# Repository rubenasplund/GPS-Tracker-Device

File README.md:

# GPS Tracker Device

## Project

The purpose for this project is to make a GPS tracker device which tracks position and movement patterns on animlas or things. Then sends the position data through lora.

## Areas of expertise

- Ruben will do the software
- Simon Will do the hardware

## Dependencies
- Install rust [https://rustup.rs/](https://rustup.rs/)

- Rust 1.40, or later

- `rustup update`

- `rustup target add thumbv7em-none-eabihf`

## Debug and Run

- `openocd -f openocd.cfg`

- `cargo run`

## Components

* GPS module - Adafruit 746 - https://www.elfa.se/en/mtk3339-gps-breakout-adafruit-746/p/30091220?q=GPS&pos=2&origPos=5&origPageSize=10&track=true

* Micro USB connector - https://www.elfa.se/en/micro-usb-with-solder-tabs-micro-usb-socket-right-angle-poles-molex-105017-0001/p/30161483?queryFromSuggest=true

* A display - SSD1306 SPI - https://cdon.se/hem-tradgard/oled-display-0-96-tum-vit-128x64-pixlar-ssd1306-spi-p50506639

* Temperature sensor - TMP36FSZ - https://se.rs-online.com/web/p/temperature-sensors-humidity-sensors/0412973/

* LED SMD 0805 - https://www.elfa.se/en/smd-led-640nm-0805-150mcd-20ma-kingbright-kp-2012surc/p/17531013?queryFromSuggest=true

* ADC - Integrated in MCU

* Battery (chargable) -ICP501022UPM - https://www.elfa.se/sv/litiumjonpolymerbatteripack-340mah-7v-renata-icp422339pr/p/30158712?q=&pos=1&origPos=1&origPageSize=10&track=true

* Charging circuit (for battery)- MCP73831T-2ACI/OT https://www.elfa.se/sv/laddkrets-75-sot-23-microchip-mcp73831t-2aci-ot/p/17386933?track=true&no-cache=true

* Button - https://www.elfa.se/en/tactile-switch-b3fs-1no-47n-6mm-omron-electronic-components-b3fs-1012p/p/30156578?q=smd+button&pos=3&origPos=43&origPageSize=100&track=true

* Power switch - https://www.elfa.se/en/low-power-slide-switch-1co-on-on-pcb-smd-rnd-components-rnd-210-00603/p/30152627?q=power+switch&pos=3&origPos=1&origPageSize=10&track=true

* Regulator lm1117 ADJ - https://se.rs-online.com/web/p/low-dropout-voltage-regulators/8472888/

* Current limiter - RT9742EGJ5 - https://www.digikey.se/product-detail/en/richtek-usa-inc/RT9742EGJ5/1028-1432-2-ND/5880515

* Diode (prevents currents going wrong way) - https://www.elfa.se/en/schottky-diode-1a-40v-do-214ac-sma-vishay-ss14-e3-61t/p/30048133

* Coax connector - https://www.elfa.se/en/micro-coaxial-straight-socket-micro-coaxial-connector-50ohm-6ghz-molex-73412-0110/p/30076410?queryFromSuggest=true

* Pin connectors to display and the GPS module - https://www.elfa.se/en/straight-male-pcb-header-through-hole-rows-10-contacts-54mm-pitch-rnd-connect-rnd-205-00631/p/30093651?q=&pos=1&origPos=1&origPageSize=10&track=true

* Pin connector to the battery - https://www.elfa.se/sv/kk-254-rak-hane-kretskortslist-genomgaende-hal-rader-kontakter-54mm-stiftavstand-molex-22-29-2021/p/30048774

* Pin female connector - https://www.elfa.se/en/straight-female-pcb-receptacle-through-hole-rows-10-contacts-54mm-pitch-rnd-connect-rnd-205-00650/p/30093670?queryFromSuggest=true

## Also needed for project

* Anti aliasing filters for sampling.

* Amplifiers to amplify eventually low signals to be measurable.

* ADC with at least 8 bits.

## TMP36FSZ

* Voltage range (100mV - 1750 mV)

* Temperature range -40 - 125 degrees

## Needed changes on pcb layout

* Add buttons on the MCU reset and also on the OLED reset, (alternatively connect them to the same reset button) 

## References

* https://github.com/mcci-catena/HW-Designs/blob/master/Boards/Catena-4610/234001131b_(Catena-4610-Schematic).pdf

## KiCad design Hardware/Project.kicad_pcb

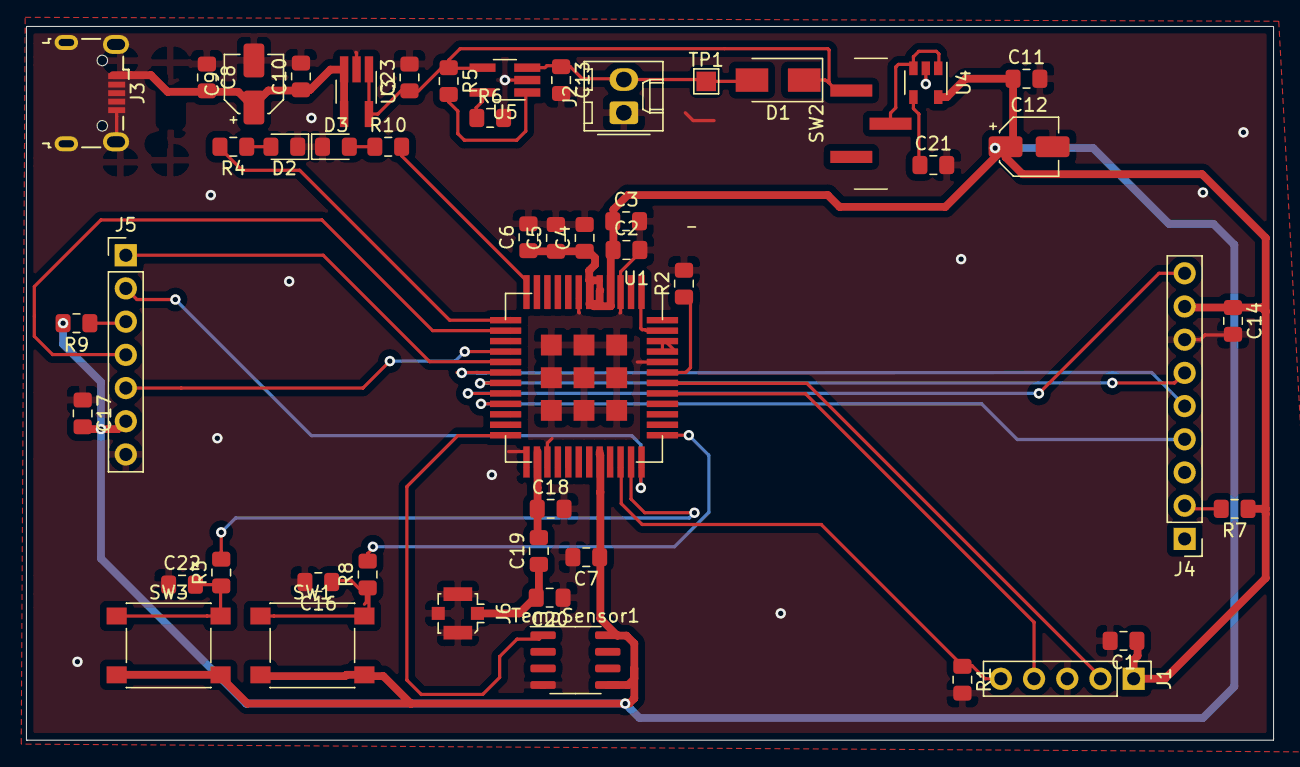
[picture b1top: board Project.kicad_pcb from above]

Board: 2 copper layers, 95.4 x 54.6 mm, 50 parts (0 on the bottom side), 36 nets.

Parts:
C1, C3, C6, C8, C10, C11, C23: 100nF; C_0805_2012Metric_Pad1.15x1.40mm_HandSolder
C2, C5, C13, C14, C18, C20: 100n; C_0805_2012Metric_Pad1.15x1.40mm_HandSolder
C4: 10uF; C_0805_2012Metric_Pad1.15x1.40mm_HandSolder
C7: 1uF; C_0805_2012Metric_Pad1.15x1.40mm_HandSolder
C9, C12: 10uF; CP_Elec_4x4.5
C16, C17, C22: 10u; C_0805_2012Metric_Pad1.15x1.40mm_HandSolder
C19: 100p; C_0805_2012Metric_Pad1.15x1.40mm_HandSolder
C21: C; C_0805_2012Metric_Pad1.15x1.40mm_HandSolder
D1: B140-E3; D_SMA
D2, D3: LED; LED_0805_2012Metric_Pad1.15x1.40mm_HandSolder
J1: Conn_01x05_Male; PinHeader_1x05_P2.54mm_Vertical
J2: Conn_01x02_Male; Molex_KK-254_AE-6410-02A_1x02_P2.54mm_Vertical
J3: USB_OTG; USB_Micro-B_Wuerth_629105150521
J4: Connection For GPS Module; PinHeader_1x09_P2.54mm_Vertical
J5: Connection for OLED Display; PinHeader_1x07_P2.54mm_Vertical
J6: Conn_Coaxial; U.FL_Molex_MCRF_73412-0110_Vertical
R1, R2, R7: 10k; R_0805_2012Metric_Pad1.15x1.40mm_HandSolder
R3, R5, R8, R9: 1k; R_0805_2012Metric_Pad1.15x1.40mm_HandSolder
R4, R10: 680; R_0805_2012Metric_Pad1.15x1.40mm_HandSolder
R6: 10K; R_0805_2012Metric_Pad1.15x1.40mm_HandSolder
SW1, SW3: SW_Push; SW_Push_1P1T_NO_6x6mm_H9.5mm
SW2: SW_SPDT; Power_Switch_cuuul
TP1: TestPoint; TestPoint_Pad_1.5x1.5mm
TempSensor1: TMP36xS; SOIC-8_3.9x4.9mm_P1.27mm
U1: CMWX1ZZABZ-078; CMWX1ZZABZ_longer_padz
U3: RT9701; TSOT-23-5_HandSoldering
U4: SPX3819M5-L-3-3; SOT-23-5
U5: MCP73831-2-OT; TSOT-23-5_HandSoldering

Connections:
+3V3: C1.1, C2.1, C3.1, C4.1, C5.1, C6.1, C7.1, C11.1, C12.1, C14.1, C17.2, J1.1, J4.8, J5.6, R7.1, R9.2, SW1.2, SW3.2, TempSensor1.5, TempSensor1.8, U1.4, U1.5, U1.6, U1.32, U4.5
+5V: C8.2, C9.1, C10.1, J3.1, U3.3, U3.4
GND: C1.2, C2.2, C3.2, C4.2, C5.2, C6.2, C7.2, C8.1, C9.2, C10.2, C11.2, C12.2, C13.2, C14.2, C16.2, C17.1, C18.2, C20.1, C21.2, C22.1, C23.2, D2.1, D3.1, J1.3, J2.1, J3.5, J3.6, J4.7, J5.7, J6.2, R1.2, R2.2, R6.2, TempSensor1.4, U1.3, U1.7, U1.25, U1.27, U1.44, U1.49, U1.50, U1.51, U1.52, U1.53, U1.54, U1.55, U1.56, U1.57, U3.2, U4.2, U5.2
unnamed: C13.1, D1.2, J2.2, TP1.1, U5.3
unnamed: C16.1, R8.1, SW1.1
unnamed: C18.1, C19.2, U1.26
unnamed: C19.1, C20.2, J6.1
unnamed: C21.1, U4.4
unnamed: C22.2, R3.1, SW3.1
unnamed: C23.1, D1.1, R5.1, SW2.1, U3.1, U3.5, U5.4
unnamed: D2.2, R4.1
unnamed: D3.2, R10.1
unnamed: J1.2, U1.42
unnamed: J1.4, U1.41
unnamed: J1.5, R1.1, U1.34
unnamed: J4.2, R7.2
unnamed: J4.4, U1.21
unnamed: J4.5, U1.18
unnamed: J4.6, U1.19
unnamed: J4.9, U1.20
unnamed: J5.1, U1.17
unnamed: J5.2, U1.36
unnamed: J5.3, R9.1
unnamed: J5.4, U1.14
unnamed: J5.5, U1.16
unnamed: R2.1, U1.43
unnamed: R3.2, U1.35
unnamed: R4.2, U1.13
unnamed: R5.2, U5.1
unnamed: R6.1, U5.5
unnamed: R8.2, U1.37
unnamed: R10.2, U1.12
unnamed: SW2.2, U4.1, U4.3
unnamed: TempSensor1.1, U1.24
unnamed: U1.1, U1.47
unnamed: U1.45, U1.46

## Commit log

2020-02-07 update.readme
2020-02-10 added data-sheets
2020-02-10 update
    Added datasheet for current limiter
2020-02-11 Update
    Added coax connector to readme
2020-04-01 Added gps software
2020-04-02 Added led pwm
2020-04-03 Added led toggle with adc signal
2020-04-03 Added button
2020-04-04 Added hardware
